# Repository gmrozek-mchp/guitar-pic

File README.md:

# Guitar Hero Bot

An autonomous robot that plays Guitar Hero / Rock Band on a Nintendo Wii by watching the game video, detecting notes in real time, and pressing the buttons on a real Wii guitar controller.

The system is built around a SAM9X75 host (**marvin**) that captures HDMI directly off the Wii, runs reference computer-vision note detection, schedules chord and strum timing, and sends fret/strum commands over USB CDC to a small actuator MCU (**fretboard**) that drives the controller's buttons via open-drain GPIO. A separate Python tool (**fret-tuner**) is used at the bench for calibration and detector tuning, but is not in the runtime path.

For the full system overview see [SPEC.md](SPEC.md).

## Where to start

| If you want to… | Read |
|---|---|
| Understand the whole system | [SPEC.md](SPEC.md) |
| Work on the SAM9X75 host (capture, CV, timing, UI) | [firmware/marvin/docs/spec.md](firmware/marvin/docs/spec.md) + [journal](firmware/marvin/docs/journal.md) |
| Work on the actuator MCU (sensors, GPIO output) | [firmware/fretboard/SPEC.md](firmware/fretboard/SPEC.md) |
| Tune detection algorithms at the bench | [tools/fret-tuner/SPEC.md](tools/fret-tuner/SPEC.md) |
| Inspect marvin performance logs (live or captured) | [tools/marvin-perf/](tools/marvin-perf/) |
| Work on actuator mechanical / PCB / 3D-print parts | [hardware/](hardware/) |

## Repository layout

```
guitar-pic/
├── README.md            # this file
├── SPEC.md              # system spec
├── CLAUDE.md            # workflow rules for Claude Code sessions
├── firmware/
│   ├── marvin/          # SAM9X75 host firmware
│   ├── fretboard/       # PIC32CM6408 sensor/actuator MCU
│   └── sam9x75_curiosity_emirror/   # Microchip reference (template only)
├── tools/
│   ├── fret-tuner/      # Python dev/calibration tool
│   └── marvin-perf/     # marvin performance-log decoder + web viewer
├── hardware/            # PCB, mechanical, actuator design
└── docs/
    ├── SAM9X7-Series-Data-Sheet-DS60001813.pdf
    └── archive/         # historical docs from the original architecture
```

## Status

Working end-to-end: marvin captures HDMI (480p60 and 720p60) and displays live on the LVDS panel; the reference CV detector (`cv_marvin_v1`) runs on captured frames; the timing pipeline and fretboard link (USB CDC over EDBG) are up and gameplay has been tested on Expert and Easy difficulty. The perf-log USB CDC export streams RTOS analytics and pixel strips to a browser-based viewer (`tools/marvin-perf`). Fretboard standalone play (phototransistors + open-drain GPIO) remains operational as a fallback.

In progress: SD-card reference-data recording (M4), full operator UI (M5+). Phasing detail in [SPEC.md §7](SPEC.md).

## License & acknowledgments

MIT License. Hobby / educational project. Guitar Hero and Rock Band are trademarks of Activision and Harmonix; Wii is a trademark of Nintendo.

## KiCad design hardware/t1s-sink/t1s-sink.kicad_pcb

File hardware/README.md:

# hardware/

Physical-build artifacts for the guitar-playing robot — PCB, mechanical, and actuator design.

| Folder | What's there |
|---|---|
| [`actuators/`](actuators/) | Design + test-protocol docs for three candidate fret/strum actuator types. The actuator choice is intentionally still open. |
| [`3d-models/`](3d-models/) | OpenSCAD sources and STLs for printed actuator parts. |
| [`Sensor-LCD5/`](Sensor-LCD5/) | KiCad project for the fretboard sensor/actuator PCB (5 phototransistors + open-drain GPIO outputs to a Wii guitar controller). |
| [`kicad/`](kicad/) | Shared KiCad symbol and footprint libraries used by `Sensor-LCD5/` and any future boards. |

## Actuator candidates

Three options are documented under `actuators/`. Each has a design doc and a test-protocol doc.

| Type | Pros | Tradeoffs |
|---|---|---|
| **Voice coil** ([design](actuators/voice-coil-design.md), [test](actuators/voice-coil-test-protocol.md)) | Quietest, fastest, supports proportional control | Most complex to build; custom-wound coil + magnet |
| **Electromagnet** ([design](actuators/electromagnet-design.md), [test](actuators/electromagnet-test-protocol.md)) | Very quiet, simple construction, no moving driver coil | Lower force per watt than a solenoid |
| **DIY solenoid** ([design](actuators/diy-solenoid-design.md)) | Well-understood, predictable behavior | Loudest of the three |

Test protocols measure response time, force, and acoustic noise so the candidates can be compared apples-to-apples before a final pick.

## How this folder relates to firmware

The actuator design docs describe physical drive characteristics (force, response time, current draw). They do not describe the software command path — that lives in the firmware specs:

- The actuator's GPIO-side interface (open-drain pin assignment, pulse durations) is defined by [`firmware/fretboard/SPEC.md`](../firmware/fretboard/SPEC.md).
- The chord and strum scheduling that produces those pulses is described by [`firmware/marvin/docs/spec.md`](../firmware/marvin/docs/spec.md) §4.4.

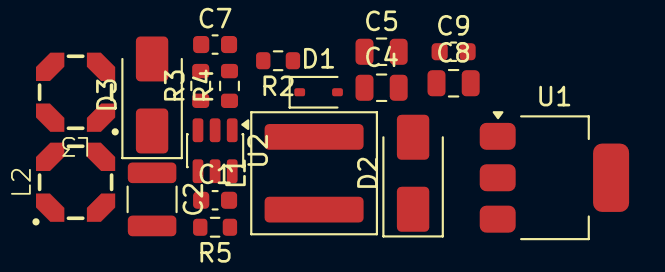
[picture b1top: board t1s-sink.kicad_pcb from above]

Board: 2 copper layers, 19 parts (0 on the bottom side), 12 nets, no tracks yet.

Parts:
C1, C9: 0.1uF 50V; C_0603_1608Metric
C2: 10uF 50V; C_1210_3225Metric
C4, C5, C8: 10uF 16V; C_0805_2012Metric
C7: 120pF 50V; C_0603_1608Metric
D1: 1N4148WS; D_SOD-323
D2, D3: MBRA140T3G; D_SMA
L1: 22uH 5A; L_Coilcraft_XAL6060-XXX
L2: 33uH, 0.31A; LPD4012
L3: 33uH 0.31A; LPD4012
R2: 52.3k; R_0603_1608Metric
R3: 4.7; R_0603_1608Metric
R4: 10.0k; R_0603_1608Metric
R5: 82; R_0603_1608Metric
U1: MCP1804x-3302xDB; SOT-223-3_TabPin2
U2: MCP16301x-xCH; SOT-23-6

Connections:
+3.3V: C8.1, C9.1, U1.1 (OUT)
+5V: C4.1, C5.1, D1.2 (A), L1.2, R2.1, U1.3 (IN)
GND: C2.2, C4.2, C5.2, C7.2, C8.2, C9.2, D2.2 (A), L3.3, R4.2, U1.2 (GND), U2.2 (GND)
unnamed: C1.1, R5.2
unnamed: C7.1, R3.2
unnamed: D1.1 (K), R5.1, U2.1 (BOOST)
unnamed: C1.2, D2.1 (K), L1.1, U2.6 (SW)
unnamed: D3.2 (A), L3.2
unnamed: L2.2, L3.1
unnamed: L2.4, L3.4
unnamed: R2.2, R3.1, R4.1, U2.3 (Vfb)
VBUS: C2.1, D3.1 (K), U2.4 (EN), U2.5 (V_{IN})

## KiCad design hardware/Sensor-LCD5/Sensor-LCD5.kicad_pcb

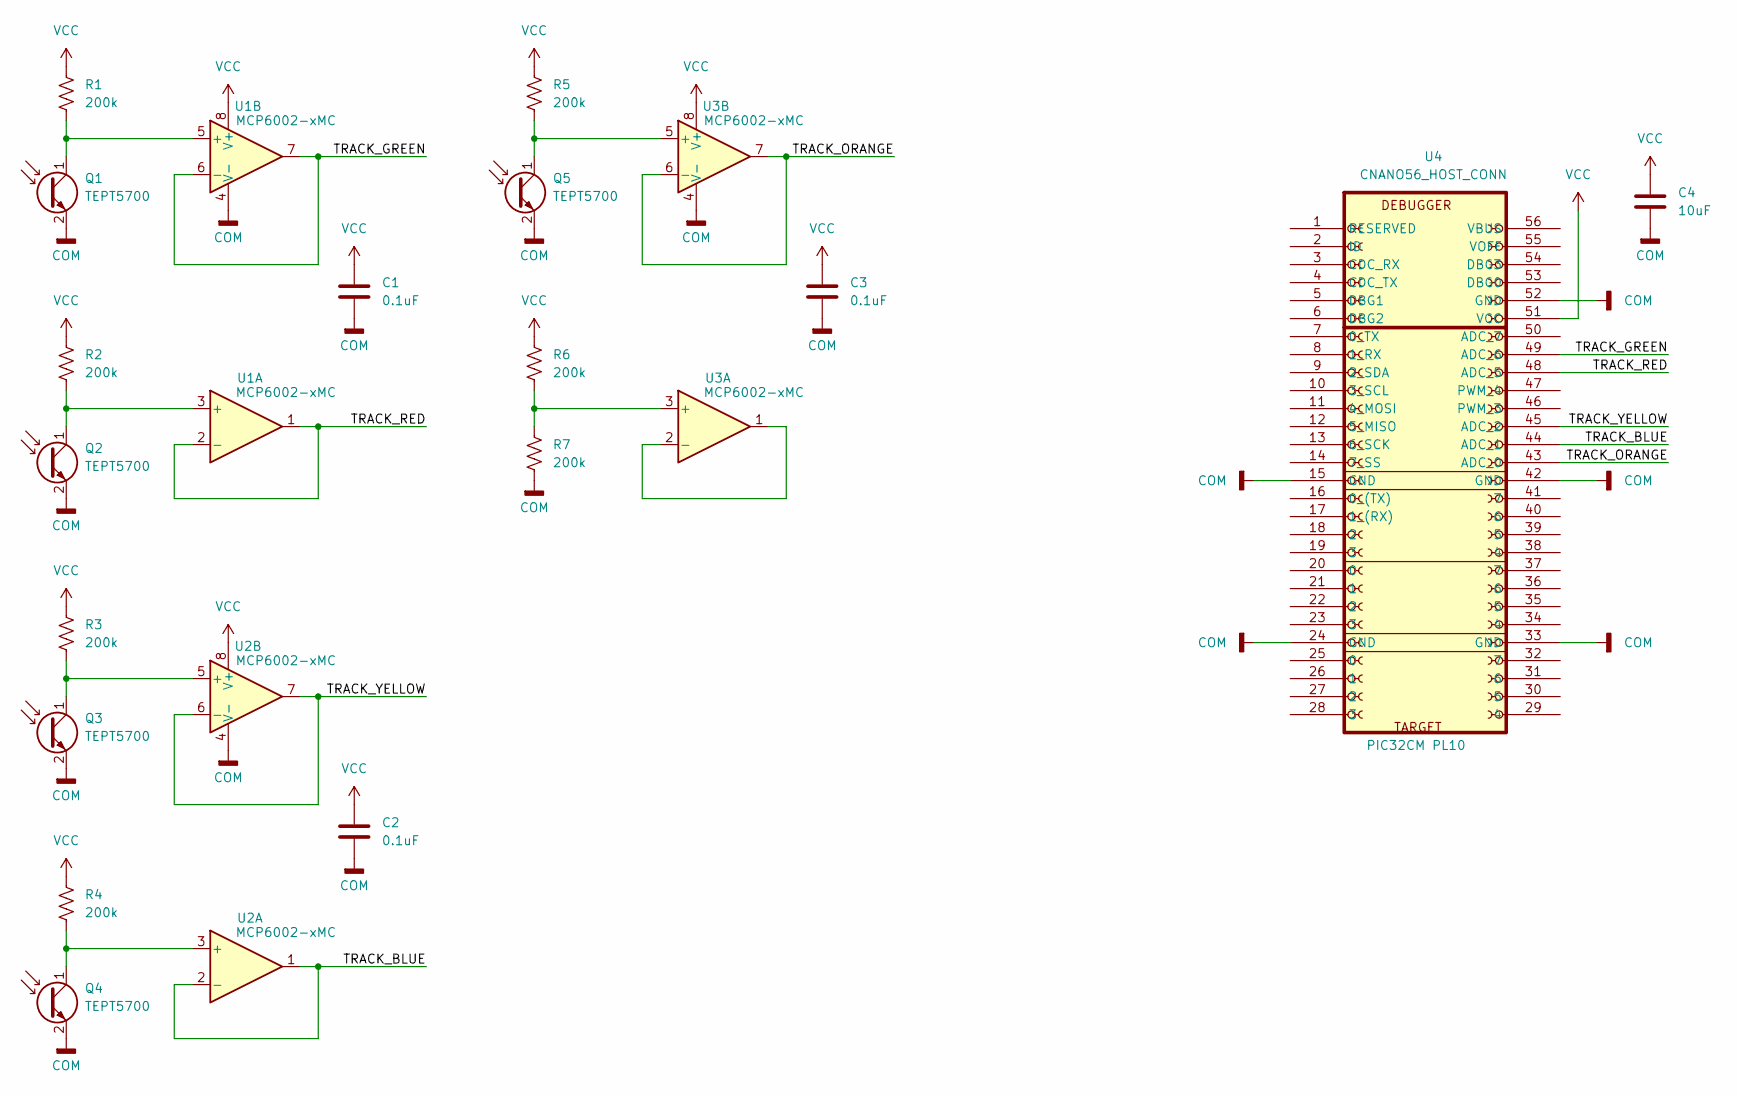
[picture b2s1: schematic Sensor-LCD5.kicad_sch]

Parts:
C1, C2, C3: 0.1uF; C_0603_1608Metric
C4: 10uF; C_0805_2012Metric
Q1, Q2, Q3, Q4, Q5: TEPT5700; LED_D5.0mm_FlatTop
R1, R2, R3, R4, R5, R6, R7: 200k; R_0603_1608Metric
U1, U2, U3: MCP6002-xMC; DFN-8-1EP_3x2mm_P0.5mm_EP1.75x1.45mm
U4: PIC32CM PL10; CNANO_Connector_56; PARTGROUP Mechanical devices,Connectors,Pin heade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

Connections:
/TRACK_BLUE: U2.1, U2.2 (-), U4.44 (ADC_1)
/TRACK_GREEN: U1.6 (-), U1.7, U4.49 (ADC_6)
/TRACK_ORANGE: U3.6 (-), U3.7, U4.43 (ADC_0)
/TRACK_RED: U1.1, U1.2 (-), U4.48 (ADC_5)
/TRACK_YELLOW: U2.6 (-), U2.7, U4.45 (ADC_2)
COM: C1.2, C2.2, C3.2, C4.2, Q1.2 (E), Q2.2 (E), Q3.2 (E), Q4.2 (E), Q5.2 (E), R7.2, U1.4 (V-), U1.9 (V-), U2.4 (V-), U2.9 (V-), U3.4 (V-), U3.9 (V-), U4.15 (GND), U4.24 (GND), U4.33 (GND), U4.42 (GND), U4.52 (GND)
unnamed: Q1.1 (C), R1.2, U1.5 (+)
unnamed: Q2.1 (C), R2.2, U1.3 (+)
unnamed: Q3.1 (C), R3.2, U2.5 (+)
unnamed: Q4.1 (C), R4.2, U2.3 (+)
unnamed: Q5.1 (C), R5.2, U3.5 (+)
unnamed: R6.2, R7.1, U3.3 (+)
unnamed: U3.1, U3.2 (-)
VCC: C1.1, C2.1, C3.1, C4.1, R1.1, R2.1, R3.1, R4.1, R5.1, R6.1, U1.8 (V+), U2.8 (V+), U3.8 (V+), U4.51 (VCC)

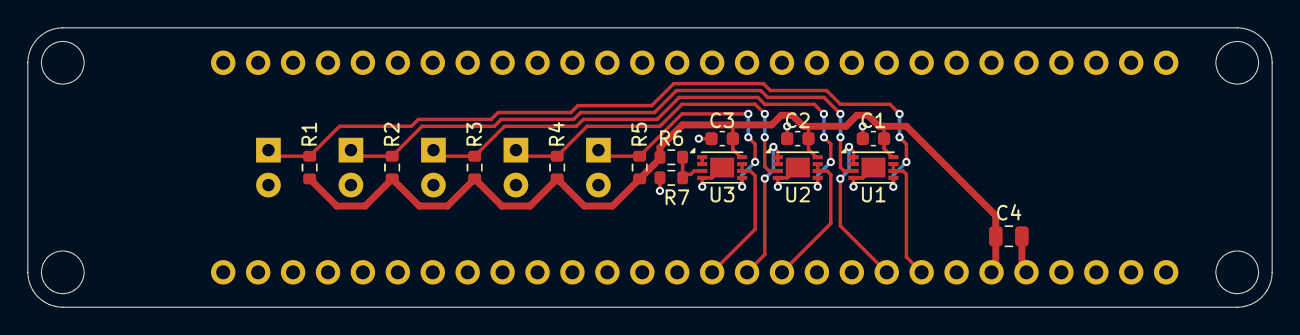
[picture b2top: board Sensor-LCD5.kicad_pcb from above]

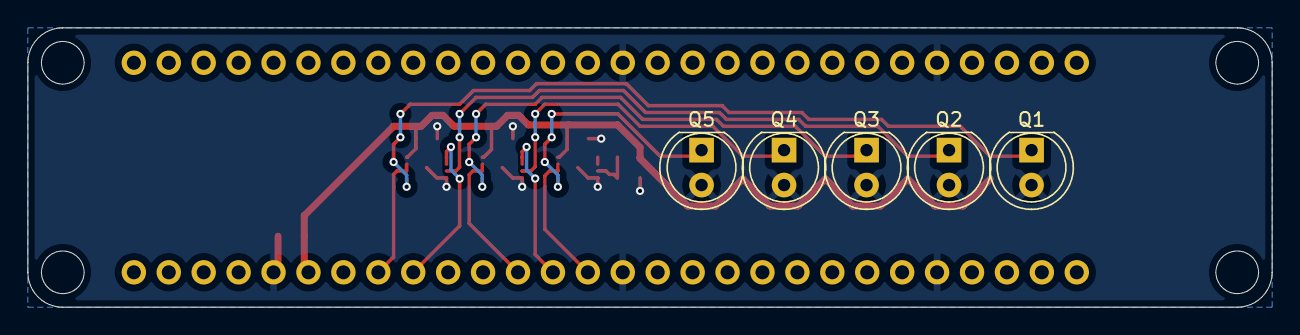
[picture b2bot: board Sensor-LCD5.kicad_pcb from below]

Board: 2 copper layers, 90.5 x 20.3 mm, 20 parts (5 on the bottom side), 14 nets.

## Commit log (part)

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2026-06-25 Increase FreeRTOS heap size.
2026-06-26 specstory
2026-06-30 Minor cleanup of song selection screen.
